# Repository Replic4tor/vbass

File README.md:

# vbass

## Hardware
We are using kicad for the pcb design. And the pcb design itself lives in the subfolder pcb. There you will find the *.kicad_sch for schematics and *.kicad_pcb for the board layout itself.

The following hardware parts are used:
- ESP32-WROOM-32
  - DAC for audio
  - ADCs for potis
  - DINs for buttons and touch inputs
  - DOUTs for LEDs
  - ... for rotator input
- ...

## Software

## Drawio Test

Anleitung fürs Einbinden der Diagramme hier: https://github.com/philip-gai/github-drawio-demo#using-appdiagramsnet

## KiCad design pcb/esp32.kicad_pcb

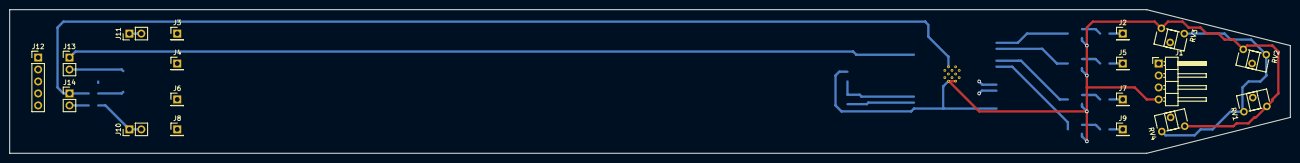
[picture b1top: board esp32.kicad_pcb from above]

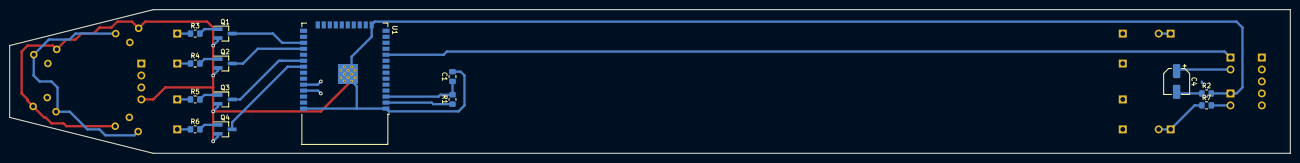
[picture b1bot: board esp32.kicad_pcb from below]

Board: 2 copper layers, 271.8 x 30.5 mm, 32 parts (14 on the bottom side), 24 nets.

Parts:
C1: 1u; C_0805_2012Metric_Pad1.18x1.45mm_HandSolder
C4: 250u; CP_Elec_5x3
J1: Conn_01x04; PinHeader_1x04_P2.54mm_Horizontal
J2, J3, J4, J5, J6, J7, J8, J9: Conn_01x01; PinHeader_1x01_P2.54mm_Vertical
J10, J11, J13, J14: Conn_01x02; PinHeader_1x02_P2.54mm_Vertical
J12: Conn_01x05; PinHeader_1x05_P2.54mm_Vertical
Q1, Q2, Q3, Q4: BC817; SOT-23_Handsoldering
R1: 10K; R_0805_2012Metric_Pad1.20x1.40mm_HandSolder
R2: 10; R_0805_2012Metric_Pad1.20x1.40mm_HandSolder
R3, R4, R5, R6, R7: 1K; R_0805_2012Metric_Pad1.20x1.40mm_HandSolder
RV1, RV2, RV3, RV4: R_Potentiometer; Potentiometer_ACP_CA6-H2,5_Horizontal
U1: ESP32-WROOM-32

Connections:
+3.3V: J14.2, R1.1, R7.2, RV1.1, RV2.1, RV3.1, RV4.1, U1.2 (VDD)
/Boot selection: J1.1, U1.25 (IO0)
/Potis/ADC1_CH6: RV3.2, U1.6 (IO34)
/Potis/ADC1_CH7: RV4.2, U1.7 (IO35)
/RXD: J1.3, U1.34 (RXD0/IO3)
/TXD: J1.2, U1.35 (TXD0/IO1)
DAC1: J13.1, U1.10 (IO25)
DIN1: Q1.3 (C), U1.27 (IO16)
DIN2: Q2.3 (C), U1.28 (IO17)
DIN3: Q3.3 (C), U1.30 (IO18)
DIN4: Q4.3 (C), U1.31 (IO19)
GND: C1.2, J1.4, J14.1, Q1.2 (E), Q2.2 (E), Q3.2 (E), Q4.2 (E), R2.2, RV1.3, RV2.3, RV3.3, RV4.3, U1.1 (GND), U1.15 (GND), U1.38 (GND), U1.39 (GND)
unnamed: C4.2, R2.1
unnamed: J10.1, J10.2, J11.1, J11.2, R7.1
unnamed: C4.1, J13.2
unnamed: Q1.1 (B), R3.2
unnamed: Q2.1 (B), R4.2
unnamed: Q3.1 (B), R5.2
unnamed: Q4.1 (B), R6.2
unnamed: C1.1, R1.2, U1.3 (EN)
SAITE_1: J2.1, R3.1
SAITE_2: J5.1, R4.1
SAITE_3: J7.1, R5.1
SAITE_4: J9.1, R6.1

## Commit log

2023-06-29 Update LICENSE
2023-06-29 drawiotest
2023-06-29 Unbenanntes Diagramm.drawio aktualisiert
2023-06-29 testbild.svg eingefügt
2023-06-29 testbild.svg aktualisiert
2023-07-01 initial pcb project for kicad
2023-07-01 added some hw infos
2023-07-08 * Initial commit of platformio project for ESP
2023-07-08 * Added examples.md
2023-07-09 * Added dependency on `DacESP32` for DAC interfacing * Added DAC example
2023-07-09 * Added AIN example
2023-07-09 * Using MusicManager for mario theme song
2023-07-20 * Added basic gameplay description
2023-07-20 * First draft of game loop
2023-07-20 * First skeleton of play loop and classes
2023-07-21 * Improved on game logic skeleton, now interfacing with speaker and two potis
2023-07-21 * First attempt at soundbits
2023-07-21 * Proper implementation of quiz manager
2023-07-21 * Added button debouncing
2023-07-21 * Improvements to logging and playback speed reader
2023-07-22 * Added ISR for rotary encoder * Added library dependency for rotary encoder
2023-07-22 * Proper rotary switch inputs
2023-07-22 * Fixed initialization bug
2023-07-22 * Better logging * Fixed state transition bug
2023-07-22 * Removed TODO
2023-07-22 * More TODOs * Increased tolerance
2024-04-15 added some componentes to schematics and pcb
2024-05-24 added CAD render images
